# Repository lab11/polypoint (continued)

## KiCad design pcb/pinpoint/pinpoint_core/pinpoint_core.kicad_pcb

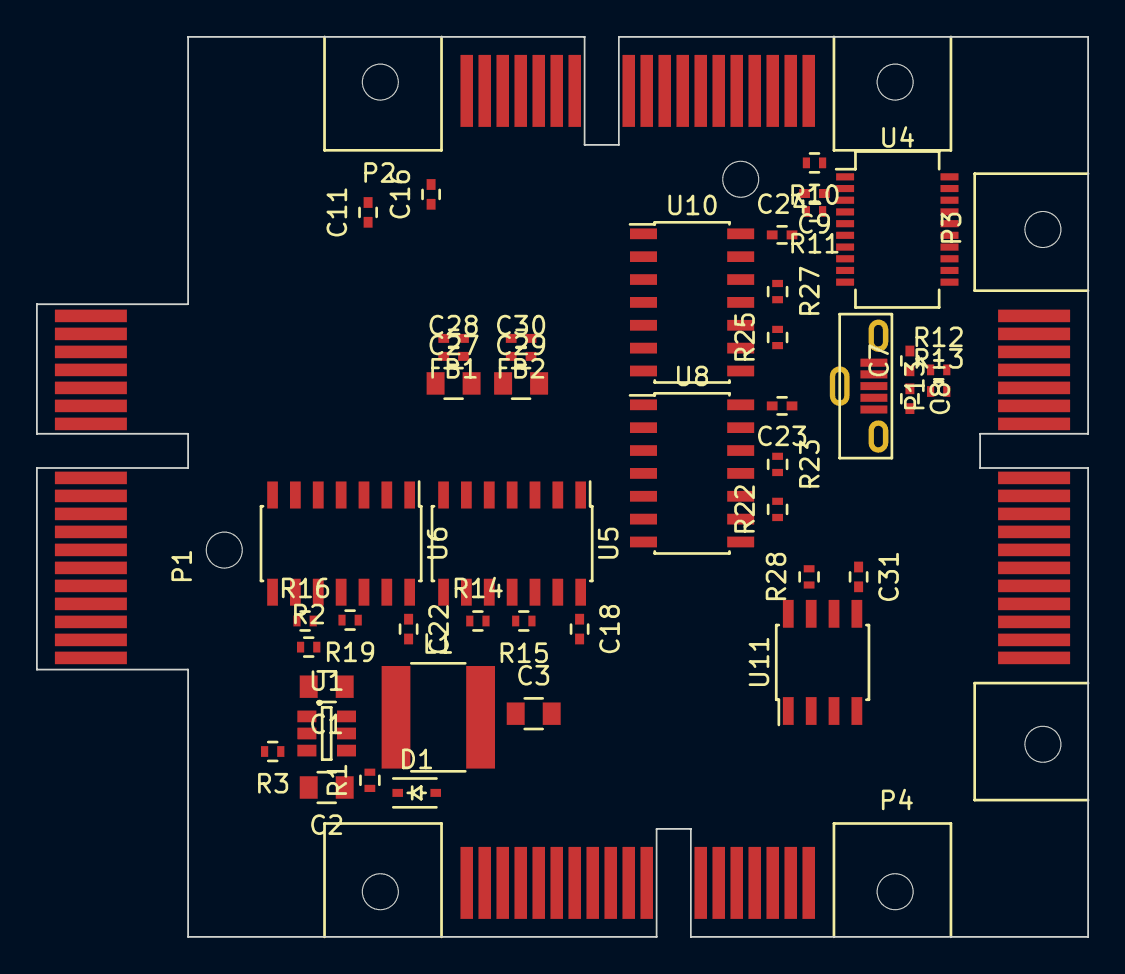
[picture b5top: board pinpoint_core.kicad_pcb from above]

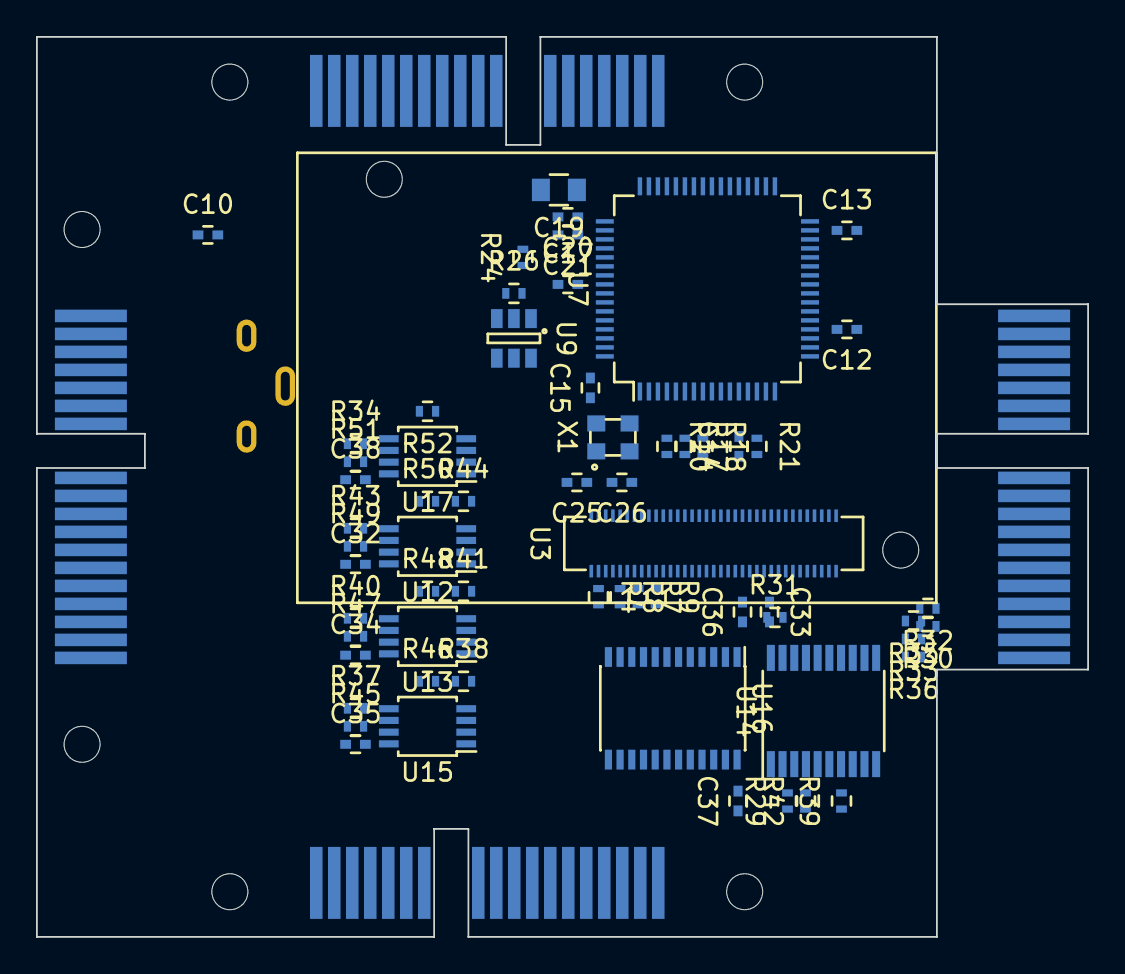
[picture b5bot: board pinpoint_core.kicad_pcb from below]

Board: 2 copper layers, 58.4 x 50.0 mm, 111 parts (62 on the bottom side), 108 nets, no tracks yet.

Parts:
C1, C2, C19, C27, C29: 4.7uF; C_0805
C3: 10uF; C_0805
C7, C8: 47pF; C_0402
C9, C10, C11, C12, C13, C14, C15, C16, C17, C18, C20, C21, C22, C23, C24, C28, C30, C31: 0.1uF; C_0402
C25, C26: 30pF; C_0402
C32, C33, C34, C35, C36, C37, C38: C_Small; C_0402
D1: D_Schottky_Small; SOD-323
FB1, FB2: FILTER; C_0402
L1: 22uH; INDUCTOR_6.0mm_6.0mm
P1: CONN_02X18; PCIx_36pos_Card_Edge
P2, P3, P4: CONN_02X18; PCIx_36pos
P13: USB_B; USB_Micro-B_Vert
R1: 0; R_0402
R2: 49.9K; R_0402
R3: 15.8K; R_0402
R4, R7, R8, R9, R21: 10K; R_0402
R10, R11: 100; R_0402
R12, R13: 27; R_0402
R14, R15, R16, R19, R22, R23, R25, R27: DNP; R_0402
R17, R18: 10; R_0402
R20: 12K/1%; R_0402
R24, R28: R_Small; R_0402
R26: 2K; R_0402
R29, R30, R31, R32, R33, R34, R35, R36, R37, R38, R39, R40, R41, R42, R43, R44: 1K; R_0402
R45, R46, R47, R48, R49, R50, R51, R52: 290; R_0402
U1: AOZ1282CI; SOT-23-6
U3: INTEL_EDISON
U4: FT231XS; SSOP-20_6.0x8.7mm_Pitch0.65mm
U5, U6, U8, U10: SN65MLVD207D; SOIC-14_3.9x8.7mm_Pitch1.27mm
U7: FT4232; LQFP-64_10x10mm_Pitch0.5mm
U9: 93LC56B; SOT-23-6
U11: ICS574; SOIC-8_3.9x4.9mm_Pitch1.27mm
U12, U13, U15, U17: P82B96-PP; TSSOP-8_3x3mm_Pitch0.65mm
U14: PCA9545A; TSSOP-20_4.4x6.5mm_Pitch0.65mm
U16: SN74AVCH8T245; TSSOP-24_4.4x7.8mm_Pitch0.65mm
X1: CRYSTAL_SMD_4; XTAL_2.50mm_2.00mm_4PAD

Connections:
+1V8: C9.1, R7.2, R9.2, U3.12, U4.3, U4.14
+3V3: C3.1, C12.2, C13.2, C16.2, C17.2, C18.1, C21.1, C22.1, C23.1, C24.1, C31.2, C33.2, C37.2, FB1.1, FB2.1, L1.2, R2.1, R8.2, R21.2, R24.2, R33.1, R34.1, R35.1, R36.1, R37.1, R38.1, R39.1, R40.1, R41.1, R42.1, R43.1, R44.1, U3.2, U3.4, U3.6, U3.14, U5.4, U5.13, U5.14, U6.4, U6.13, U6.14, U7.20, U7.31, U7.42, U7.50, U7.56, U8.4, U8.13, U8.14, U9.6, U10.4, U10.13, U10.14, U11.5, U14.20, U16.23, U16.24
+5V: C10.1, P13.1, U4.15
+15V: C32.2, C34.2, C35.2, P1.11, P1.12, P2.11, P2.12, P3.11, P3.12, P4.11, P4.12, R45.1, R46.1, R47.1, R48.1, R49.1, R50.1, R51.1, R52.1, U12.8, U13.8, U15.8
+36V: C2.1, P1.1, P1.2, P1.3, P1.4, P1.5, P1.6, P1.7, P1.8, P1.9, P1.10, P2.1, P2.2, P2.3, P2.4, P2.5, P2.6, P2.7, P2.8, P2.9, P2.10, P3.1, P3.2, P3.3, P3.4, P3.5, P3.6, P3.7, P3.8, P3.9, P3.10, P4.1, P4.2, P4.3, P4.4, P4.5, P4.6, P4.7, P4.8, P4.9, P4.10, R1.1, U1.5
/PinPoint Bus Switch/CFG0_IN0: P1.25, U16.3
/PinPoint Bus Switch/CFG0_IN1: P1.27, U16.4
/PinPoint Bus Switch/CFG0_OUT1: U3.25, U16.20
/PinPoint Bus Switch/CFG1_IN0: U3.26, U16.5
/PinPoint Bus Switch/CFG1_IN1: U3.28, U16.6
/PinPoint Bus Switch/CFG1_OUT0: P2.25, U16.19
/PinPoint Bus Switch/CFG1_OUT1: P2.27, U16.18
/PinPoint Bus Switch/CFG2_IN0: U3.30, U16.7
/PinPoint Bus Switch/CFG2_IN1: U3.32, U16.8
/PinPoint Bus Switch/CFG2_OUT0: P3.25, U16.17
/PinPoint Bus Switch/CFG2_OUT1: P3.27, U16.16
/PinPoint Bus Switch/CFG3_IN0: U3.34, U16.9
/PinPoint Bus Switch/CFG3_IN1: U3.42, U16.10
/PinPoint Bus Switch/CFG3_OUT0: P4.25, U16.15
/PinPoint Bus Switch/CFG3_OUT1: P4.27, U16.14
/PinPoint Bus Switch/I2C0_SCL: P1.29, R49.2, U12.7
/PinPoint Bus Switch/I2C0_SDA: P1.23, R50.2, U12.1
/PinPoint Bus Switch/I2C1_SCL: P2.29, R47.2, U13.7
/PinPoint Bus Switch/I2C1_SDA: P2.23, R48.2, U13.1
/PinPoint Bus Switch/I2C2_SCL: P3.29, R45.2, U15.7
/PinPoint Bus Switch/I2C2_SDA: P3.23, R46.2, U15.1
/PinPoint Bus Switch/I2C3_SCL: P4.29, R51.2, U17.7
/PinPoint Bus Switch/I2C3_SDA: P4.23, R52.2, U17.1
/PinPoint Bus Switch/I2C_IN_SCL: R31.2, U3.45, U14.18
/PinPoint Bus Switch/I2C_IN_SDA: R32.2, U3.47, U14.19
/PinPoint Edison/CFG0: U3.24, U16.21
/PinPoint Edison/USB_D+: R18.2, U3.16
/PinPoint Edison/USB_D-: R17.2, U3.18
/PinPoint Serial/MISO0_D+: P1.28, R15.1, U5.12
/PinPoint Serial/MISO0_D-: P1.30, R15.2, U5.11
/PinPoint Serial/MISO1_D+: P2.24, R19.1, U6.12
/PinPoint Serial/MISO1_D-: P2.26, R19.2, U6.11
/PinPoint Serial/MISO2_D+: P3.24, R23.1, U8.12
/PinPoint Serial/MISO2_D-: P3.26, R23.2, U8.11
/PinPoint Serial/MISO3_D+: P4.24, R27.1, U10.12
/PinPoint Serial/MISO3_D-: P4.26, R27.2, U10.11
/PinPoint Serial/MOSI0_D+: P1.26, R14.1, U5.9
/PinPoint Serial/MOSI0_D-: P1.24, R14.2, U5.10
/PinPoint Serial/MOSI1_D+: P2.28, R16.1, U6.9
/PinPoint Serial/MOSI1_D-: P2.30, R16.2, U6.10
/PinPoint Serial/MOSI2_D+: P3.28, R22.1, U8.9
/PinPoint Serial/MOSI2_D-: P3.30, R22.2, U8.10
/PinPoint Serial/MOSI3_D+: P4.28, R25.1, U10.9
/PinPoint Serial/MOSI3_D-: P4.30, R25.2, U10.10
/PinPoint Splitter/REF_IN: P1.16, U11.1
/PinPoint Splitter/REF_OUT0: P2.16, U11.2, U11.8
/PinPoint Splitter/REF_OUT1: P3.16, U11.3
/PinPoint Splitter/REF_OUT2: P4.16, U11.6
/PinPoint Splitter/SYNC_IN: P1.20, P2.20, P3.20, P4.20
GND: C2.2, C3.2, C7.2, C8.2, C9.2, C10.2, C11.1, C12.1, C13.1, C14.1, C15.1, C16.1, C17.1, C18.2, C19.2, C20.2, C21.2, C22.2, C23.2, C24.2, C25.2, C26.2, C27.2, C28.2, C29.2, C30.2, C31.1, C32.1, C33.1, C34.1, C35.1, C36.2, C37.1, C38.1, D1.2, P1.13, P1.14, P1.15, P1.17, P1.18, P1.19, P1.21, P1.22, P2.13, P2.14, P2.15, P2.17, P2.18, P2.19, P2.21, P2.22, P3.13, P3.14, P3.15, P3.17, P3.18, P3.19, P3.21, P3.22, P4.13, P4.14, P4.15, P4.17, P4.18, P4.19, P4.21, P4.22, P13.4, P13.5, R3.2, R4.2, R20.2, R28.2, U1.2, U3.1, U3.5, U3.9, U3.11, U3.13, U3.15, U4.6, U4.16, U5.3, U5.6, U5.7, U6.3, U6.6, U6.7, U7.1, U7.5, U7.10, U7.11, U7.13, U7.15, U7.25, U7.35, U7.47, U7.51, U8.3, U8.6, U8.7, U9.2, U10.3, U10.6, U10.7, U11.4, U12.4, U13.4, U14.1, U14.2, U14.10, U15.4, U16.11, U16.12, U16.13, U16.22, U17.4, X1.2, X1.4
unnamed: C1.1, D1.1, L1.1, U1.6
unnamed: C1.2, U1.1
unnamed: C7.1, P13.2, R12.1
unnamed: C8.1, P13.3, R13.1
unnamed: C11.2, C14.2, C15.2, C19.1, C20.1, U7.12, U7.37, U7.49, U7.64
unnamed: C25.1, U7.2, X1.1
unnamed: C26.1, U7.3, X1.3
unnamed: C38.2, U17.8
unnamed: R1.2, U1.4
unnamed: R2.2, R3.1, U1.3
unnamed: R4.1, U3.3
unnamed: R7.1, R8.1, U3.17
unnamed: R9.1, U3.19
unnamed: R10.1, U4.20
unnamed: R10.2, U3.22
unnamed: R11.1, U4.4
unnamed: R11.2, U3.27
unnamed: R12.2, U4.12
unnamed: R13.2, U4.11
unnamed: R17.1, U7.7
unnamed: R18.1, U7.8
unnamed: R20.1, U7.6
unnamed: R21.1, U7.14
unnamed: R24.1, R26.2, U9.1
unnamed: R26.1, U7.61, U9.3
unnamed: R28.1, U11.7
unnamed: R29.2, U14.3
unnamed: R30.2, U14.17
unnamed: R33.2, U14.14
unnamed: R34.2, U14.16, U17.5, U17.6
unnamed: R35.2, U14.15, U17.2, U17.3
unnamed: R36.2, U14.11
unnamed: R37.2, U14.13, U15.5, U15.6
unnamed: R38.2, U14.12, U15.2, U15.3
unnamed: R39.2, U14.7
unnamed: R40.2, U13.5, U13.6, U14.9
unnamed: R41.2, U13.2, U13.3, U14.8
unnamed: R42.2, U14.4
unnamed: R43.2, U12.5, U12.6, U14.6
unnamed: R44.2, U12.2, U12.3, U14.5
unnamed: U5.2, U7.17
unnamed: U5.5, U7.16
unnamed: U6.2, U7.27
unnamed: U6.5, U7.26
unnamed: U7.38, U8.5
unnamed: U7.39, U8.2
unnamed: U7.62, U9.4
unnamed: U7.63, U9.5
unnamed: U7.52, U10.2
unnamed: U7.48, U10.5
VDDDIG: C36.1, R29.1, R30.1, R31.1, R32.1, U16.1, U16.2
VPHY: C29.1, C30.1, FB2.2, U7.4
VPLL: C27.1, C28.1, FB1.2, U7.9

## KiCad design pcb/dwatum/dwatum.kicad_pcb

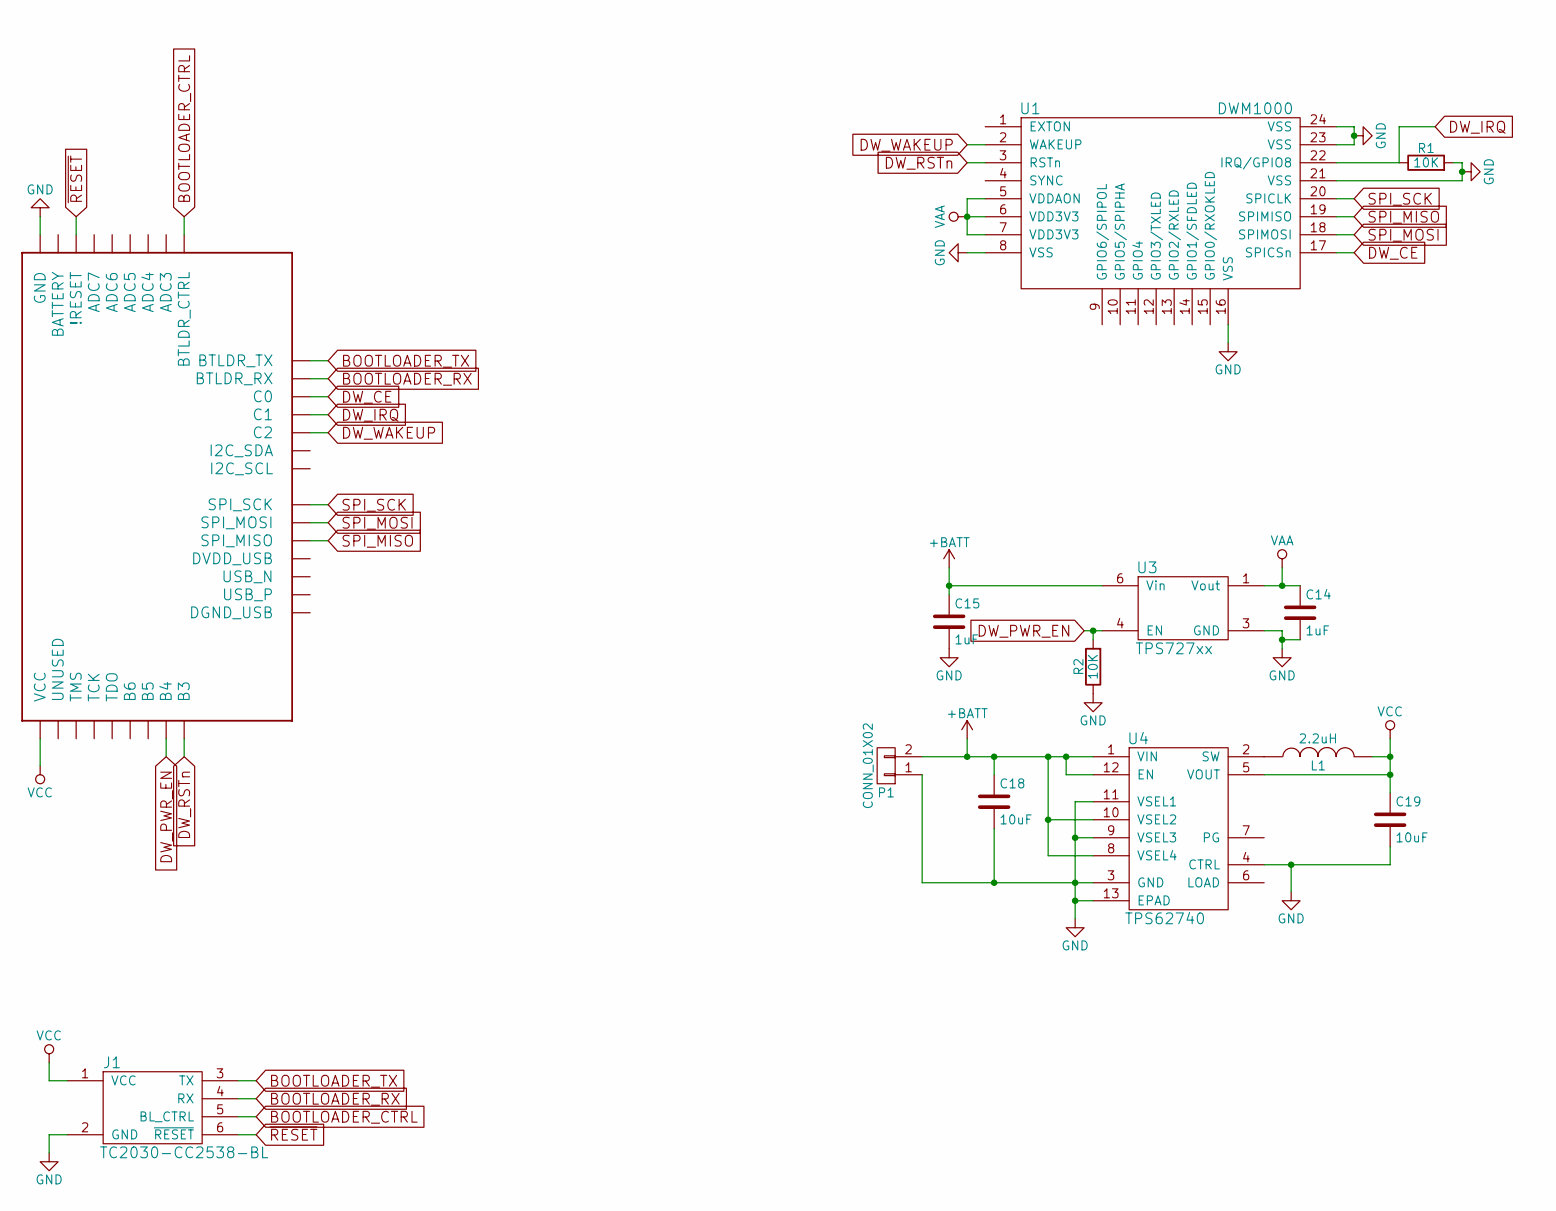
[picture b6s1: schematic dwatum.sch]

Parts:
C14, C15: 1uF; C_0402
C18, C19: 10uF; C_0603
J1: TC2030-CC2538-BL; TC2030
L1: 2.2uH; MIPSZ201D
P1: CONN_01X02; Pin_Header_Straight_1x02
R1, R2: 10K; R_0402
U1: DWM1000; DWM1000_REVERSE_SMD
U2: ATUM; ATUM_SMD
U3: TPS727xx; WSON-8_1.5x1.5mm
U4: TPS62740; R-PWSON-12

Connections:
+BATT: C15.1, C18.1, P1.2, U3.6 (Vin), U4.1 (VIN), U4.8 (VSEL4), U4.10 (VSEL2), U4.12 (EN)
BOOTLOADER_CTRL: J1.5 (BL_CTRL), U2.24 (BTLDR_CTRL)
BOOTLOADER_RX: J1.4 (RX), U2.22 (BTLDR_RX)
BOOTLOADER_TX: J1.3 (TX), U2.23 (BTLDR_TX)
DW_CE: U1.17 (SPICSn), U2.21 (C0)
DW_IRQ: R1.1, U1.22 (IRQ/GPIO8), U2.20 (C1)
DW_PWR_EN: R2.2, U2.8 (B4), U3.4 (EN)
DW_RSTn: U1.3 (RSTn), U2.9 (B3)
DW_WAKEUP: U1.2 (WAKEUP), U2.19 (C2)
GND: C14.2, C15.2, C18.2, C19.2, J1.2 (GND), P1.1, R1.2, R2.1, U1.8 (VSS), U1.16 (VSS), U1.21 (VSS), U1.23 (VSS), U1.24 (VSS), U2.32 (GND), U3.3 (GND), U4.3 (GND), U4.4 (CTRL), U4.9 (VSEL3), U4.11 (VSEL1), U4.13 (EPAD)
unnamed: L1.1, U4.2 (SW)
SPI_MISO: U1.19 (SPIMISO), U2.14 (SPI_MISO)
SPI_MOSI: U1.18 (SPIMOSI), U2.15 (SPI_MOSI)
SPI_SCK: U1.20 (SPICLK), U2.16 (SPI_SCK)
VAA: C14.1, U1.5 (VDDAON), U1.6 (VDD3V3), U1.7 (VDD3V3), U3.1 (Vout)
VCC: C19.1, J1.1 (VCC), L1.2, U2.1 (VCC), U4.5 (VOUT)
~RESET: J1.6 (~RESET), U2.30 (!RESET)

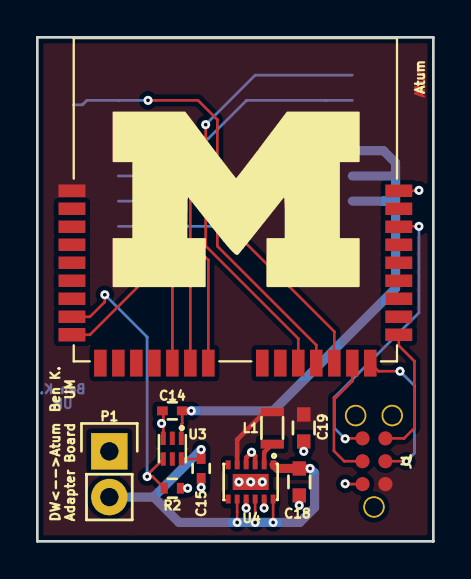
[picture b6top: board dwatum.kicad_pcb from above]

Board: 2 copper layers, 22.0 x 28.0 mm, 13 parts (1 on the bottom side), 17 nets.

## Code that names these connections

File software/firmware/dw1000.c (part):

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
	// SPI pin mappings
	GPIO_PinAFConfig(SPI1_SCK_GPIO_PORT,  SPI1_SCK_SOURCE,  SPI1_SCK_AF);
	GPIO_PinAFConfig(SPI1_MOSI_GPIO_PORT, SPI1_MOSI_SOURCE, SPI1_MOSI_AF);
	GPIO_PinAFConfig(SPI1_MISO_GPIO_PORT, SPI1_MISO_SOURCE, SPI1_MISO_AF);

	// Configure SPI pins
	GPIO_InitStructure.GPIO_Mode  = GPIO_Mode_AF;
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	GPIO_Init(SPI1_SCK_GPIO_PORT, &GPIO_InitStructure);

	// SPI MOSI pin configuration
	GPIO_InitStructure.GPIO_Pin = SPI1_MOSI_PIN;
	GPIO_Init(SPI1_MOSI_GPIO_PORT, &GPIO_InitStructure);

	// SPI MISO pin configuration
	GPIO_InitStructure.GPIO_Pin = SPI1_MISO_PIN;
	GPIO_Init(SPI1_MISO_GPIO_PORT, &GPIO_InitStructure);

	// SPI NSS pin configuration
	GPIO_InitStructure.GPIO_Mode = GPIO_Mode_OUT;
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	// Enable GPIOA clock
	RCC_AHBPeriphClockCmd(DW_INTERRUPT_CLK, ENABLE);

	// Configure PA0 pin as input floating
	GPIO_InitStructure.GPIO_Pin = DW_INTERRUPT_PIN;
	GPIO_InitStructure.GPIO_Mode = GPIO_Mode_IN;
	GPIO_InitStructure.GPIO_PuPd = GPIO_PuPd_NOPULL;
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
	// Setup wakeup pin.
	RCC_AHBPeriphClockCmd(DW_WAKEUP_CLK, ENABLE);
	GPIO_InitStructure.GPIO_Pin = DW_WAKEUP_PIN;
	GPIO_InitStructure.GPIO_Mode = GPIO_Mode_OUT;
	GPIO_InitStructure.GPIO_OType = GPIO_OType_PP;
	GPIO_InitStructure.GPIO_Speed = GPIO_Speed_50MHz;
	GPIO_InitStructure.GPIO_PuPd = GPIO_PuPd_NOPULL;
	GPIO_Init(DW_WAKEUP_PORT, &GPIO_InitStructure);
	GPIO_WriteBit(DW_WAKEUP_PORT, DW_WAKEUP_PIN, Bit_RESET);

	// Make the reset pin output
	GPIO_InitStructure.GPIO_Pin = DW_RESET_PIN;
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	RCC_AHBPeriphClockCmd(ANT_SEL1_CLK, ENABLE);
	RCC_AHBPeriphClockCmd(ANT_SEL2_CLK, ENABLE);

	GPIO_InitStructure.GPIO_Pin = ANT_SEL0_PIN;
	GPIO_InitStructure.GPIO_Mode = GPIO_Mode_OUT;
	GPIO_InitStructure.GPIO_OType = GPIO_OType_PP;
	GPIO_InitStructure.GPIO_Speed = GPIO_Speed_50MHz;
	GPIO_InitStructure.GPIO_PuPd = GPIO_PuPd_NOPULL;
	GPIO_Init(ANT_SEL0_PORT, &GPIO_InitStructure);

	GPIO_InitStructure.GPIO_Pin = ANT_SEL1_PIN;
	GPIO_InitStructure.GPIO_Mode = GPIO_Mode_OUT;
	GPIO_InitStructure.GPIO_OType = GPIO_OType_PP;
	GPIO_InitStructure.GPIO_Speed = GPIO_Speed_50MHz;
	GPIO_InitStructure.GPIO_PuPd = GPIO_PuPd_NOPULL;
	GPIO_Init(ANT_SEL1_PORT, &GPIO_InitStructure);

	GPIO_InitStructure.GPIO_Pin = ANT_SEL2_PIN;
	GPIO_InitStructure.GPIO_Mode = GPIO_Mode_OUT;
	GPIO_InitStructure.GPIO_OType = GPIO_OType_PP;
	GPIO_InitStructure.GPIO_Speed = GPIO_Speed_50MHz;
	GPIO_InitStructure.GPIO_PuPd = GPIO_PuPd_NOPULL;
	GPIO_Init(ANT_SEL2_PORT, &GPIO_InitStructure);

	// Initialize the RF Switch
	GPIO_WriteBit(ANT_SEL0_PORT, ANT_SEL0_PIN, Bit_SET);
	GPIO_WriteBit(ANT_SEL1_PORT, ANT_SEL1_PIN, Bit_RESET);
	GPIO_WriteBit(ANT_SEL2_PORT, ANT_SEL2_PIN, Bit_RESET);

	// Pre-populate DMA fields that don't need to change
	DMA_InitStructure.DMA_PeripheralBaseAddr = (uint32_t) SPI1_DR_ADDRESS;
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}


// HW interrupt for the interrupt pin from the DW1000
void EXTI2_3_IRQHandler (void) {
	if (EXTI_GetITStatus(EXTI_Line2) != RESET) {
		// Mark this interrupt as had occurred in the main thread.
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// Main thread interrupt handler for the interrupt from the DW1000. Basically
// just passes knowledge of the interrupt on to the DW1000 library.
void dw1000_interrupt_fired () {
	// Keep calling the decawave interrupt handler as long as the interrupt pin
	// is asserted, but add an escape hatch so we don't get stuck forever.
	uint8_t count = 0;
	do {
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	// Antenna selection comes from the STM32 chip instead of the DW1000 now

	// Set all of them low
	GPIO_WriteBit(ANT_SEL0_PORT, ANT_SEL0_PIN, Bit_RESET);
	GPIO_WriteBit(ANT_SEL1_PORT, ANT_SEL1_PIN, Bit_RESET);
	GPIO_WriteBit(ANT_SEL2_PORT, ANT_SEL2_PIN, Bit_RESET);

	// Set the one we want high
	switch (antenna_number) {
		case 0: GPIO_WriteBit(ANT_SEL0_PORT, ANT_SEL0_PIN, Bit_SET); break;
		case 1: GPIO_WriteBit(ANT_SEL1_PORT, ANT_SEL1_PIN, Bit_SET); break;
		case 2: GPIO_WriteBit(ANT_SEL2_PORT, ANT_SEL2_PIN, Bit_SET); break;
	}
}

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	// Assert the WAKEUP pin. There seems to be some weirdness where a single
	// WAKEUP assert can get missed, so we do it multiple times to make
	// sure the DW1000 is awake.
	GPIO_WriteBit(DW_WAKEUP_PORT, DW_WAKEUP_PIN, Bit_SET);
	uDelay(1000);
	GPIO_WriteBit(DW_WAKEUP_PORT, DW_WAKEUP_PIN, Bit_RESET);
	uDelay(100);
	GPIO_WriteBit(DW_WAKEUP_PORT, DW_WAKEUP_PIN, Bit_SET);
	uDelay(1000);
	GPIO_WriteBit(DW_WAKEUP_PORT, DW_WAKEUP_PIN, Bit_RESET);
	uDelay(100);
	GPIO_WriteBit(DW_WAKEUP_PORT, DW_WAKEUP_PIN, Bit_SET);
	uDelay(1000);
	GPIO_WriteBit(DW_WAKEUP_PORT, DW_WAKEUP_PIN, Bit_RESET);
	uDelay(100);
	GPIO_WriteBit(DW_WAKEUP_PORT, DW_WAKEUP_PIN, Bit_SET);
	uDelay(1000);
	GPIO_WriteBit(DW_WAKEUP_PORT, DW_WAKEUP_PIN, Bit_RESET);

	// Now wait for 5ms for the chip to move from the wakeup to the idle
	// state. The datasheet says 4ms, but we buffer a little in case things
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
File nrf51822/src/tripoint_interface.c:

#include "nrf_drv_twi.h"
#include "sdk_errors.h"
#include "app_util_platform.h"
#include "nrf_drv_config.h"
#include "nrf_drv_gpiote.h"
#include "nrf_delay.h"

#include "boards.h"
#include "led.h"

#include "tripoint_interface.h"

uint8_t response[256];

nrf_drv_twi_t twi_instance = NRF_DRV_TWI_INSTANCE(1);

// Save the callback that we use to signal the main application that we
// received data over I2C.
tripoint_interface_data_cb_f _data_callback = NULL;


void tripoint_interrupt_handler (nrf_drv_gpiote_pin_t pin, nrf_gpiote_polarity_t action) {
	// verify interrupt is from tripoint
	if (pin == TRIPOINT_INTERRUPT_PIN) {
		// Ask whats up over I2C
		uint32_t ret;
		uint8_t cmd = TRIPOINT_CMD_READ_INTERRUPT;
		ret = nrf_drv_twi_tx(&twi_instance, TRIPOINT_ADDRESS, &cmd, 1, false);
		if (ret != NRF_SUCCESS) return;

		// Figure out the length of what we need to receive by
		// checking the first byte of the response.
		uint8_t len = 0;
		ret = nrf_drv_twi_rx(&twi_instance, TRIPOINT_ADDRESS, &len, 1, true);
		if (ret != NRF_SUCCESS) return;

		// Read the rest of the packet
		if (len == 0) {
			// some error?
		} else {
			ret = nrf_drv_twi_rx(&twi_instance, TRIPOINT_ADDRESS, response, len, false);
			if (ret != NRF_SUCCESS) return;
		}

		// Send back the I2C data
		_data_callback(response, len);
	}
}

ret_code_t tripoint_hw_init () {
	nrf_drv_twi_config_t twi_config;
	ret_code_t ret;

	// Initialize the I2C module
	twi_config.sda                = I2C_SDA_PIN;
	twi_config.scl                = I2C_SCL_PIN;
	twi_config.frequency          = NRF_TWI_FREQ_400K;
	twi_config.interrupt_priority = APP_IRQ_PRIORITY_HIGH;

	ret = nrf_drv_twi_init(&twi_instance, &twi_config, NULL);
	if (ret != NRF_SUCCESS) return ret;
	nrf_drv_twi_enable(&twi_instance);

	// Initialize the GPIO interrupt from the device
	ret = nrf_drv_gpiote_init();
	if (ret != NRF_SUCCESS) return ret;

	nrf_drv_gpiote_in_config_t in_config = GPIOTE_CONFIG_IN_SENSE_LOTOHI(true);
	ret = nrf_drv_gpiote_in_init(TRIPOINT_INTERRUPT_PIN, &in_config, tripoint_interrupt_handler);
	if (ret != NRF_SUCCESS) return ret;

	nrf_drv_gpiote_in_event_enable(TRIPOINT_INTERRUPT_PIN, true);
	return NRF_SUCCESS;
}

ret_code_t tripoint_init (tripoint_interface_data_cb_f cb) {
	_data_callback = cb;
	ret_code_t ret;

	// Wait for 500 ms to make sure the tripoint module is ready
	nrf_delay_us(500000);

	// Now try to read the info byte to make sure we have I2C connection
	{
		uint16_t id;
		uint8_t version;
		ret = tripoint_get_info(&id, &version);
		if (ret != NRF_SUCCESS) return ret;
		if (id != TRIPOINT_ID) return NRF_ERROR_INVALID_DATA;
	}

	return NRF_SUCCESS;
}

ret_code_t tripoint_get_info (uint16_t* id, uint8_t* version) {
	uint8_t buf_cmd[1] = {TRIPOINT_CMD_INFO};
	uint8_t buf_resp[3];
	ret_code_t ret;

	// Send outgoing command that indicates we want the device info string
	ret = nrf_drv_twi_tx(&twi_instance, TRIPOINT_ADDRESS, buf_cmd, 1, false);
	if (ret != NRF_SUCCESS) return ret;

	// Read back the 3 byte payload
	ret = nrf_drv_twi_rx(&twi_instance, TRIPOINT_ADDRESS, buf_resp, 3, false);
	if (ret != NRF_SUCCESS) return ret;

	*id = (buf_resp[0] << 8) | buf_resp[1];
	*version = buf_resp[2];

	return NRF_SUCCESS;
}

ret_code_t tripoint_start_ranging (bool periodic, uint8_t rate) {
	uint8_t buf_cmd[4];
	ret_code_t ret;

	buf_cmd[0] = TRIPOINT_CMD_CONFIG;

	// TAG for now
	buf_cmd[1] = 0;

	// TAG options
	buf_cmd[2] = 0;
	if (periodic) {
		// leave 0
	} else {
		buf_cmd[2] |= 0x2;
	}

	// Use sleep mode on the TAG
	buf_cmd[2] |= 0x08;

	// And rate
	buf_cmd[3] = rate;

	ret = nrf_drv_twi_tx(&twi_instance, TRIPOINT_ADDRESS, buf_cmd, 4, false);
	if (ret != NRF_SUCCESS) return ret;

	return NRF_SUCCESS;
}

// Tell the attached TriPoint module to become an anchor.
ret_code_t tripoint_start_anchor (bool is_glossy_master) {
	uint8_t buf_cmd[4];
	ret_code_t ret;

	buf_cmd[0] = TRIPOINT_CMD_CONFIG;

	// Make ANCHOR
	if(is_glossy_master)
		buf_cmd[1] = 0x01 | 0x20;
	else
		buf_cmd[1] = 0x01;

	// // TAG options
	// buf_cmd[2] = 0;
	// if (periodic) {
	// 	// leave 0
	// } else {
	// 	buf_cmd[2] |= 0x2;
	// }

	// // And rate
	// buf_cmd[3] = rate;

	ret = nrf_drv_twi_tx(&twi_instance, TRIPOINT_ADDRESS, buf_cmd, 2, false);
	if (ret != NRF_SUCCESS) return ret;

	return NRF_SUCCESS;
}

// Tell the attached TriPoint module that it should enter the calibration
// mode.
ret_code_t tripoint_start_calibration (uint8_t index) {
	uint8_t buf_cmd[4];
	ret_code_t ret;

	buf_cmd[0] = TRIPOINT_CMD_CONFIG;

	// Make TAG in CALIBRATION
	buf_cmd[1] = 0x04;

	// Set the index of the node in calibration
	buf_cmd[2] = index;

	ret = nrf_drv_twi_tx(&twi_instance, TRIPOINT_ADDRESS, buf_cmd, 3, false);
	if (ret != NRF_SUCCESS) return ret;

	return NRF_SUCCESS;
}

// Read the TriPoint stored calibration values into a buffer (must be
// at least 18 bytes long).
ret_code_t tripoint_get_calibration (uint8_t* calib_buf) {
	uint8_t buf_cmd[1] = {TRIPOINT_CMD_READ_CALIBRATION};
	ret_code_t ret;

	// Send outgoing command that indicates we want the device info string
	ret = nrf_drv_twi_tx(&twi_instance, TRIPOINT_ADDRESS, buf_cmd, 1, false);
	if (ret != NRF_SUCCESS) return ret;

	// Read back the 18 bytes of calibration values
	ret = nrf_drv_twi_rx(&twi_instance, TRIPOINT_ADDRESS, calib_buf, 18, false);
	if (ret != NRF_SUCCESS) return ret;

	return NRF_SUCCESS;
}

// Stop the TriPoint module and put it in sleep mode
ret_code_t tripoint_sleep () {
	uint8_t buf_cmd[1] = {TRIPOINT_CMD_SLEEP};
	ret_code_t ret;

	ret = nrf_drv_twi_tx(&twi_instance, TRIPOINT_ADDRESS, buf_cmd, 1, false);
	if (ret != NRF_SUCCESS) return ret;

	return NRF_SUCCESS;
}

// Restart the TriPoint module. This should only be called if the TriPoint was
// once running and then was stopped. If the TriPoint was never configured,
// this won't do anything.
ret_code_t tripoint_resume () {
	uint8_t buf_cmd[1] = {TRIPOINT_CMD_RESUME};
	ret_code_t ret;

	ret = nrf_drv_twi_tx(&twi_instance, TRIPOINT_ADDRESS, buf_cmd, 1, false);
	if (ret != NRF_SUCCESS) return ret;

	return NRF_SUCCESS;
}

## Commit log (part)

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2015-09-05 testing ranging
    there is some crap in tag code for testing. should be removed when
    things work
2015-09-05 remove debugging preset in tag
2015-09-06 actually getting packets from ~20 m
2015-09-07 updated tritag mac address
2015-09-07 set EUI more properly
    make flash ID=c0:98:e5:50:50:44:50:01
2015-09-14 fix bug with sending ranges to phone
    pointers are hard
2015-09-14 updated sleep code
    added support in tag
2015-09-14 better sleep support, settings changable
    may be able to reconfigure tripoints over i2c
2015-09-14 add on-demand ranging
2015-09-16 wakeup and reset working
    hopefully we are at least kinda resilient to sleep failures.
2015-09-16 more reset loops
    try to keep these things running
2015-09-16 small clean
2015-09-16 copy data
2015-09-17 rework how i2c is handled.
    should solve the no response problem
2015-09-17 add check to make sure we don't deadlock on int
    if dw1000 gets in "interrupt all the things!" state, we can now check
    for that and reset
2015-09-18 notify and value update working with limited testing
2015-09-18 use notify feature that works now
2015-09-18 clean up dw1000.c
    add comments
    remove old functions
    remove other unused defines
2015-09-18 little better node code
2015-09-18 slight comment change
2015-09-21 cleaning up tritag app some more
2015-09-21 need to toggle wakeup pin, not just assert it
2015-09-21 update to flash
2015-09-21 Add readme for tripoint firmware
2015-09-21 clean up delay files
2015-09-21 changes have been incorporated
2015-09-21 update readme with hardware and software
2015-09-22 reformatting .h files
    more logical
2015-09-22 update nrf5x base
2015-09-22 rename pcb files
2015-09-22 adding hw start
2015-09-22 get rid of interrupt every 5 ms
2015-09-22 another attempt to get sleep working
    no luck
2015-09-23 refactor code layout for multiple apps
    also start on calibration
    fingers crossed things still work
2015-09-23 adding gerbers for calibration brace
2015-09-23 update hardware readme
2015-09-23 add readme for tritag ble app
2015-09-23 fix issue with state machine
    reset works
2015-09-23 calibration algorithm first pass
2015-09-24 calibration seems plausible
2015-09-24 Add calibration design
2015-09-24 updated calib with 4 pkt protocol
2015-09-26 configure tritag addresses
2015-09-27 fixed array bounds issue
    reformatted notification packet
2015-09-28 slight cleanup
2015-09-28 update doc to typable characters
    colors dont make good column headers
2015-09-28 update API to what the calibration node sends back
2015-09-28 add sample data
2015-09-28 add readme for calibration
2015-09-28 no compiler warnings
2015-09-28 update some old code in nrf folder
2015-09-28 more text in api
2015-09-28 First pass at revised calibration
    Precision across many clock domains is tricky..
2015-09-29 fixing broken submodule
2015-09-29 first pass at YET ANOTHER CALIBRATION SCHEME
2015-09-29 Also add pdf of diagram
2015-09-29 update calibration script
2015-09-29 added function for calibration
    and the correct places to add the offsets
2015-09-30 fix issue with javascript numbers over 32 bit
2015-09-30 working code to test backscatter
2015-09-30 add more sample calib data
2015-09-30 update calibration doc
2015-10-01 put led back on tag
2015-10-01 update to magic check softdevice version
2015-10-01 cases
2015-10-01 move 3d models into better folders
2015-10-01 rename case to something reasonable
2015-10-01 update case links after moves
2015-10-01 updated breakout
2015-10-02 update eddystone url
2015-10-02 some hope of cordova app working
2015-10-02 add readme
2015-10-02 getting ranges notified
2015-10-03 added adv code
2015-10-03 little more cleaning on summon app
2015-10-03 getting closer to summon app extracting data
    native javascript buffer handling is awful. Give me node!
2015-10-05 breakout basically done
2015-10-05 Finish calibration script. Closes #4.
2015-10-05 calibration values over host interface
2015-10-05 Update a single calibration file
2015-10-05 check for -1 in calib data
2015-10-05 create readme for firmware folder
2015-10-05 comment in makefile
2015-10-05 remove fake calibration from code
2015-10-05 save calibration value
2015-10-06 Re-fix calibration
2015-10-06 Fix new node bug
2015-10-06 Remove unnecessary branch
2015-10-06 changes
    sorry about the commit message
2015-10-07 Set calibration distance to rig mode instead of desk mode
2015-10-07 changed print
2015-10-07 updated calib data
2015-10-07 summon app doesnt look as terrible
2015-10-08 add polypoint logo -brad
2015-10-09 fixed with new summon version
2015-10-10 bad changes to calibration log
2015-10-10 more calib data
2015-10-10 add meta
2015-10-10 bounds check in calibration
2015-10-12 update calibration folder
2015-10-12 update main readme
2015-10-13 fixing buffer overflow issue with ble notification
2015-10-13 code changes from backscatter testing
2015-10-19 added docs for tridev pcb
2015-10-20 updated pcb with different pours
2015-10-22 adding latest gerbers
2015-10-23 ui change to tridev
2015-10-23 added python script for talking to tripoint
2015-10-23 rev b of the breakout
2015-10-23 rounding corner of only 45 degree rf trace
2015-10-24 revert tridev to version that was fabbed
2015-10-26 updated i2c ftdi code
2015-11-02 accidentally committed bad code earlier
2015-11-02 actually adding CIR extraction logic this time
2015-11-10 no great results
2015-11-19 update tritag to new make system
2015-11-19 small changes to v1p2 board (cosmetic)
2015-11-20 little doc on tritag-anchor
2015-11-20 add some doc about node code
2015-11-23 add tridev note
2015-12-02 backscatter CIR is looking better
2015-12-08 wired clock sync seems to be showing promise
2015-12-08 modifying code to work with longer recordings at higher fidelity
2015-12-11 Adding operating system dependencies
2016-01-08 latest un-committed changes
2016-01-12 modifications to support bandstitching
2016-01-14 Updated to new nrf5x-base service API
2016-02-01 adding bandstitching analysis code
2016-02-10 new sanity checks in makefiles
2016-02-10 Move DEVICE_NAME #define to fix duplicate #defines
2016-02-13 An improvement upon PolyPoint's previous localization consistency and performance. First, waking DW1000 from sleep greatly hinders its immediate RX performance, so all DW1000 sleep code has been remo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
2016-02-18 uncommitted changes resulting in correct bandstitching functionality
2016-02-18 first attempt at adding uart functionality to bandstitching code
2016-02-18 up to maximum baudrate attainable (6 Mbps)
2016-02-19 adding new schematic components for timebase board
2016-02-20 working on timebase schematic. Jitter cleaner is the only thing left to include
2016-02-21 adding adapter board to test PinPoint with TriDev board
2016-02-21 minor cosmetic fixes
2016-02-21 adding gerbers for pinpoint timebase and pinpoint to tridev adapter baord
2016-02-22 adding BOMs for two PinPoint boards
2016-02-24 scripts and code for performing calibration over saleae
2016-02-24 starting from scratch with calibration data
2016-02-24 created script to process saleae traces and convert to calibration measurements
2016-02-25 a couple typos with the calibration code
2016-02-25 typo in using calibration data
2016-03-03 working UART DMA offload
2016-03-04 Fix trivial warnings in calibration.c
2016-03-04 Add header/footer to uart packets
2016-03-04 Add initial dump script
2016-03-04 Wrap whole thing in keyboardinterrupt try/except
2016-03-04 Add binary output support
2016-03-04 Report round_num; actually check footer
2016-03-04 adding rxpacc and finfo reads
2016-03-11 positive results with out_manchester_works.bin
2016-03-12 now modified to work at faster update rate (out_manchester_fast_works.bin)
2016-03-16 good results with monostatic radar setup
2016-03-22 minor modifications to support multiple antennas
2016-03-22 updating dw1000-driver
2016-03-26 fixing bugs introduced from migrating to scratchspace utilization
2016-03-26 adding candidate code for reduced bitrate, long-range code
2016-03-26 candidate code to test smarter response window sizing
2016-03-26 fixing a couple mistakes in git master rebase
2016-03-27 reliable code for low datarate, need to test for higher baud rates now
2016-03-27 fast baudrate now works as well
2016-03-27 adding UART capability
2016-03-29 adding CW test mode capability
2016-04-02 adding newly-calibrated tags
2016-04-02 master kicks off sync packets as expected
2016-04-02 initial code to test out glossy
2016-04-02 glossy achieves time sync
2016-04-02 getting closer to LPM working
2016-04-02 getting rid of depth field in sync flood
2016-04-02 Glossy PER tests are now complete
2016-04-02 fixing transmit counter overflow issues
2016-04-02 LWB appears to work!
2016-04-02 fixing ack bugs in anchor response windows
2016-04-02 finishing up tag code to do schedule requests
2016-04-03 we were past the program memory limit. got rid of calibration app which currently is not used anymroe
2016-04-03 everything seems to be in a stable enough state to start testing
2016-04-03 candidate fix for timestamp overflow issues
2016-04-03 adding code which correctly reads in uart logging output
2016-04-03 getting close with octave code
2016-04-03 overflow issue
2016-04-04 real rxoverrun issue fixed
2016-04-05 changes for doing glossy atrium tests
2016-04-05 adding new python script which interprets new glossy output data stream
2016-04-05 done with porting ranging to python
2016-04-06 bug in re-initialization of anchor after a glossy sync
2016-04-06 WIP: ranging calculation seems to be working
2016-04-06 don't die on bad range
2016-04-06 small stability changes
2016-04-06 Only locate if asked
2016-04-06 Add PID option to short set ID
2016-04-06 better anchor listening code
2016-04-06 Add anchor loc to outfile
2016-04-06 Add newline
2016-04-07 Use decawave for timestamps
2016-04-07 implement recursive iteration
2016-04-07 fixing lots of bugs that were plaguing polypoint tests
2016-04-08 Add anchor history; guly but effective
2016-04-08 Skip useless processing; add calibration
2016-04-09 adding channel model simulation
2016-04-10 channel index miscalculation
2016-04-10 new uart offload code
2016-04-20 adding PPS sync logic
2016-08-26 [old changes on disk]: Add diversity flag
2016-08-31 off-by-one in clock offset calculation
2016-09-01 fixing reliability issues in scheduleing and crystal offset compensation
2016-09-03 getting closer to correct glossy measurements, just need to incorporate real calibration data
2016-09-03 down to 16k offset.... almost there
2016-09-07 final sync code
2016-09-09 adding readme for calibration procedure
2016-09-15 fixing compilation errors
2016-09-16 adding flooding ranges back to master
2016-09-16 timer fixes that should be merged into master
2016-09-20 should use double buffer operation all the time
2016-09-20 bad to re-enable rx during rxcallback for some reason...
2016-09-20 make sure everyone is flooding on the correct channel
2016-09-23 avoid resetting anchor before flood is complete
2016-09-23 adding reporting code
2016-09-26 schedule issues when left on between master power cycles
2016-09-27 a bit better stability. Overruns not always caught though...
2016-09-29 better reliability. Still not quite there...
2016-10-03 reliability approaching nominal
2016-10-11 Add screenshot of app
2016-10-11 Add app screenshot
2016-10-13 Add test data script
2016-10-19 code used for IPSN submission
2016-10-20 python script seems to now work correctly. oct2py still giving errors though
2016-10-20 Add GDP POST to summon; add z to GDP packet
2016-10-23 (untested) pull anchor locations dynamically
2016-10-23 demo with looping history
2016-10-23 formatting anchor locations as JSON
2016-10-24 Update data_dump_glossy with attempt at GDP support
2017-02-08 Release under the Apache 2.0 License
    License terms confirmed with @bradjc and @bpkempke.
